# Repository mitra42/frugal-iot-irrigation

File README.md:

# Frugal-IoT Irrigation

This project is intended to provide solar-powered irrigation for small farms. A set of sectors is watered one at a time, once a day. 

The default version waters each sector until its soil reaches a target moisture or a time limit runs out, but it can be 
subclased for more complex per-sector requirements. 

There are tank-level and battery interlocks that stop the whole run, and this also can be customized. 

It is built on top of Frugal-IoT and both the irrigation and MPPT components draw part of their
inspiration from [OSPIT](https://www.apc.org/en/news/meet-ospit-sustainable-energy-and-irrigation-solution-community-networks)
(Lua on the FF-ESP32-OpenMPPT solar charge controller)
- [OSPIT_COMPARISON.md](OSPIT_COMPARISON.md) describes what is different and why.

This release should work in four hardware environments.

* The "FF-ESP32-OpenMPPT solar charge controller" in which case it will run MPPT 
* Our custom board in `hardware` with onboard relays and RS485. 
* A simple off the shelf dev board with hardwired sensors, just edit board definitions in 
  platformio.ini and `wiring` in frugal-iot-irrigation.ino
* A distributed sensor environment, just change the `wiring` in frugal-iot-irrigation.ino 
  to point at the distributed sensors

[Frugal-IoT](https://github.com/mitra42/frugal-iot) brings: WiFi setup from a phone; MQTT; web and phone dashboards; graphing and over-the-air updates.  

Any of the other features of Frugal-IoT can be easily added to your sketch including, off-internet operation, remote sensors, LoRa, or a wide range of other sensors for example for weather. 

## What it does today

- **Up to N irrigation sectors**, run strictly in order, one valve open at a time.
- **Soil moisture per sector** from RS485/Modbus probes sharing one bus, or from simple
  analog capacitive soil sensors.
- Anomaly handling - for instance, a sector whose probe is **not reporting is skipped**
- **Tank level** from a float sender, with two thresholds: one to begin a run, a lower one to
  abort it. "No tank sensor fitted" is kept distinct from "tank empty".
- **Battery interlock** - irrigation stops below a configurable voltage and resumes above a higher
  one.
- Optional **pump** (driven with the valves) and **load output** (e.g. for a router) (switched by the
  battery interlock) on separate pins.
- Optional **OLED**: Displays battery; sector moistures; tank and communicationss status.
- **Solar charge control** - two-stage MPPT tracking with temperature compensation, a hard
  thermal cut-out, and battery-type profiles.
- **Battery reporting** - state of charge and a health estimate inferred from voltage drop.

## Status

**None of the charge control has run on real hardware yet**, so it ships switched off. 

Run the checks in [TESTING.md](TESTING.md) and then turn on `mppt/automatic`

`HARDWARE-QUESTIONS.md` is a list of things we need someone with the OSPIT hardware to
look at and confirm.

## Hardware

Three boards are supported out of the box. See `platformio.ini` for the full pin list.

| Board | Notes |
|---|---|
| **FF-ESP32-OpenMPPT** | the solar charge controller OSPIT runs on. Pin assignments are OSPIT's own |
| **Frugal IoT Irrigation v0.1** | a custom board with Relays, RS485 and battery charging |
| **Lolin S2 Mini** | the same application on a plain dev board, no charging hardware.|
| other | Setting up support for most other boards is trivial, look in the [Frugal-IoT/examples/all](https://github.com/mitra42/frugal-iot/blob/main/examples/all/platformio.ini) for example configuration for many popular boards or [add a new issue](https://github.com/mitra42/frugal-iot-irrigation/issues/new) in this repo.

The `FF-ESP32-OpenMPTT` board has the needed functionality, but is going to be a significantly more expensive solution than the `Frugal IoT Irrigation v0.1` paired, if neccessary, with an off-the-shelf MPPT controller.

You will also need: 12 V valves and a driver for them, one Modbus soil probe per sector, an RS485
transceiver, and optionally a tank float sender and a pump.

The hardware in `hardware` is available as a full set of Gerber and fabrication files, they are designed for use at SLCPCB but could be adapted to any manufacturer (and we would
be happy to add files for other manufacturers). Note this hardware has (as of Oct 2026) yet to be built and tested. 

## Building

### PlatformIO (recommended)

```bash
pio run --environment ff_openmppt          # compile
pio run --target upload -e ff_openmppt     # flash
pio run --target uploadfs -e ff_openmppt   # upload data/ (WiFi passwords etc)
```

The Frugal-IoT library is fetched automatically, so a fresh clone needs nothing set up. 
If you are changing the library at the same time, 
see "Building against a local library" in [CLAUDE.md](CLAUDE.md).

### Arduino IDE

1. Install **Frugal-IoT** from Library Manager (or clone it into your `libraries/` folder).
2. Install the ESP32 board support package.
3. Open `frugal-iot-irrigation.ino` - the whole repository folder is the sketch folder.
4. Under **Tools > Board**, pick the board you have. `platform.h` supplies the right pins for it;
   if your board has no section there, compiling stops with a message telling you so.

`platform.h` is generated from `platformio.ini`. If you change pins there, re-run
`scripts/generate_platform_h.bash`, or the two toolchains will disagree.

## First run

1. Flash, then power up. The device makes its own WiFi network - connect a phone to it.
2. A setup page opens (or browse to `192.168.4.1`). Give it your WiFi name and password.
3. **Irrigation starts switched off.** Turn it on in the **Irrigation** section, and set
   the start time while you are there.

`TESTING.md` walks through commissioning a real board step by step, including calibrating the tank
and the battery. `HARDWARE-QUESTIONS.md` is a list of things we need someone with the OSPIT hardware to look at.

Because not everyone has sun, a multimeter and a fortnight, `docs/` holds three ready-made plans —
[bench](docs/plan-bench.md), [sunny half-day](docs/plan-sunny-session.md),
[days of running](docs/plan-long-run.md) — each a short ordered list of which Parts of `TESTING.md`
to do. Question 9 of `HARDWARE-QUESTIONS.md` picks one. [docs/sleep-test.md](docs/sleep-test.md) is
the one test that needs its own build, on the `sleep-test` branch.

## Licence

Same as Frugal-IoT. The OSPIT algorithms parts of this are derived from are GPL-2.0-or-later,
Copyright (C) 2026 Corinna 'Elektra' Aichele.

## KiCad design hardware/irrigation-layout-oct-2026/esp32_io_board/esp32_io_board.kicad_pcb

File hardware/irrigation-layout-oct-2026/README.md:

# Frugal-IoT Irrigation V0.1

An ESP32 I/O board for irrigation and similar field control: four 12 V relays, RS485 (Modbus), I2C sensors,
two spare GPIOs, and power from 12 V, USB or a single LiPo cell. Designed Oct 2026 for assembly by JLCPCB.
This folder is for review: comments and suggested changes welcome — see "Points for reviewers" below.

## The board

- 100 × 80 mm, 2 layers, 1.6 mm FR-4, 4 × M3 corner holes.
- Relays and their screw terminals along one long edge; field connectors (12 V in, RS485, I2C, GPIOs, OLED)
  along the other; USB-C on the right short edge, LiPo connector on the left.
- Surface-mount parts on the top side, assembled by JLCPCB; relays and terminals are through-hole
  (JLCPCB hand-solders them, or you can).

## Power

- Powered from **12 V** (screw terminal, up to 15 V), **5 V USB-C**, or a **local single LiPo cell** (optional,
  JST-PH, 18650 at most).
- 12 V input: reverse-polarity protection (Schottky), 15 V TVS, then a 5 V buck (AP63205). USB 5 V and the
  buck output are diode-ORed onto the 5 V rail, so either or both can be connected.
- The 5 V rail charges the cell (TP4056; 250 mA, or 500 mA with a solder jumper). The cell has its own
  protection (DW01A + FS8205A: over-charge, over-discharge, over-current/short).
- Load sharing: when 5 V is present it powers the board and the charger only charges; when 5 V goes away a
  P-FET switches the cell in. Either source then feeds a 3.3 V LDO (AP2112K, 600 mA) for the module.
- Two switched rails turned on together by one GPIO: **3V3_SW** (sensors, I2C, RS485) and **5V_SW** (RS485
  sensor supply). Both off at reset. 5V_SW only exists when 12 V or USB is present, not on battery alone.
- Monitoring: the 12 V input and the cell voltage are each read on an ADC pin.
- The relay coils run from 12 V, so **relays work only when 12 V is connected**.

## Processor

- ESP32-C6-MINI-1U module (default) or ESP32-C3-MINI-1U on the same footprint — both have a **U.FL antenna
  socket** (an external antenna is needed). Two pairs of 0 Ω links select which module's USB pins are used.
- Native USB on USB-C for programming and serial (no USB-UART chip); USB ESD protection.
- Buttons: RESET, BOOT/BTN1 (hold at reset for download mode, a normal button afterwards), BTN2 (C6 only).
- Status LED (green); charger LEDs (charging red, charged green).
- Unfitted headers for UART0 debug, a cell thermistor, and the I/O expander's spare pins.

## Outputs and interfaces

- **4 relays** (SRD-12VDC-SL-C), contacts NO/COM/NC on 5.08 mm screw terminals, isolated from the board rails.
  Rated for 12 V DC loads up to about 4–5 A per channel with this copper. Driven through an I2C I/O expander
  (TCA9534) and a ULN2003, so the relays stay off through reset and boot. A red LED per relay shows it is on.
- **RS485** (Modbus): 3.3 V transceiver, not isolated, transmit/receive switched automatically from the TX
  line; bias resistors, 120 Ω termination on a solder jumper, surge protection. Terminal: 5V_SW, A, B, GND.
- **I2C**: 4-way 2.54 mm terminal (3V3_SW, SDA, SCL, GND) plus a 4-pin OLED header (GND, 3V3_SW, SCL, SDA).
- **2 GPIOs** (GPIO_A — ADC capable — and GPIO_B, C6 only) on 2-way 2.54 mm terminals with GND, with
  unfitted pull-up/pull-down positions.

## Firmware notes

- Turn on RAIL_EN before any I2C traffic (relay changes included) or RS485; the expander itself is always
  powered and keeps the relays as set while the rail is off.
- Relay outputs: TCA9534 P0–P3 high = relay on. P4–P7 go to an unfitted header — drive them low if unused.
- GPIO map (module pad → use) is in DECISIONS.md, D18.

## Points for reviewers

Items that are deliberately "proposed" rather than final — opinions especially welcome:

1. RS485 direction from TX (D21): fine for Modbus at 9600 baud, marginal with long cables and two
   terminations; a true auto-direction transceiver (THVD1406) is the alternative.
2. RS485 terminal supplies 5V_SW — should it be 12 V for your sensors? (D22)
3. Cell thermistor (TEMP) disabled by default (D27); charge current 250/500 mA (D12).
4. LiPo connector: pin 1 = −, pin 2 = + (D47). JST-PH polarity is not standard — check your cells.
5. Relay contact copper ~4–5 A per channel (D50).
6. The 5.08 mm terminals use the Phoenix MKDS footprint for KF128 parts of the same pitch (D42).
7. Small bulk capacitance on 3V3_SW to limit inrush (D33).
8. Before ordering: check part rotations in JLCPCB's assembly preview (see fabrication/README.md).

## Cost (JLCPCB, Oct 2026)

About **$22 per board for 10**, **$13 per board for 100**, assembled, before shipping. Breakdown in
COST-ESTIMATE.txt; the ESP32 module is the largest single item.

## What's in this folder

| | |
|---|---|
| `README.md` | This description |
| `SCHEMATIC.pdf` | Full schematic, one sheet |
| `PCB-LAYOUT.pdf` | 3D views and both copper layers |
| `BOM.csv` | Bill of materials with LCSC (JLCPCB) part numbers |
| `COST-ESTIMATE.txt` | JLCPCB cost for 10 and 100 boards |
| `DECISIONS.md` | Every design decision, why, and what would reopen it (D1–D64) |
| `esp32_io_board/` | KiCad 10 project (schematic, PCB, project libraries) |
| `fabrication/` | Files to order from JLCPCB — see its README |
| `firmware/` | PlatformIO env for frugal-iot-irrigation + board variant (pins_arduino.h) |
| `datasheets/` | Datasheets checked during design |
| `claude-tools/` | Scripts Claude uses to regenerate and change the design — reviewers can ignore |

To suggest a change: mark up the PDFs, edit in KiCad, or describe it; the schematic is generated from
`claude-tools/schematic/circuit.py`, so changes made by Claude go there rather than into the .kicad_sch.

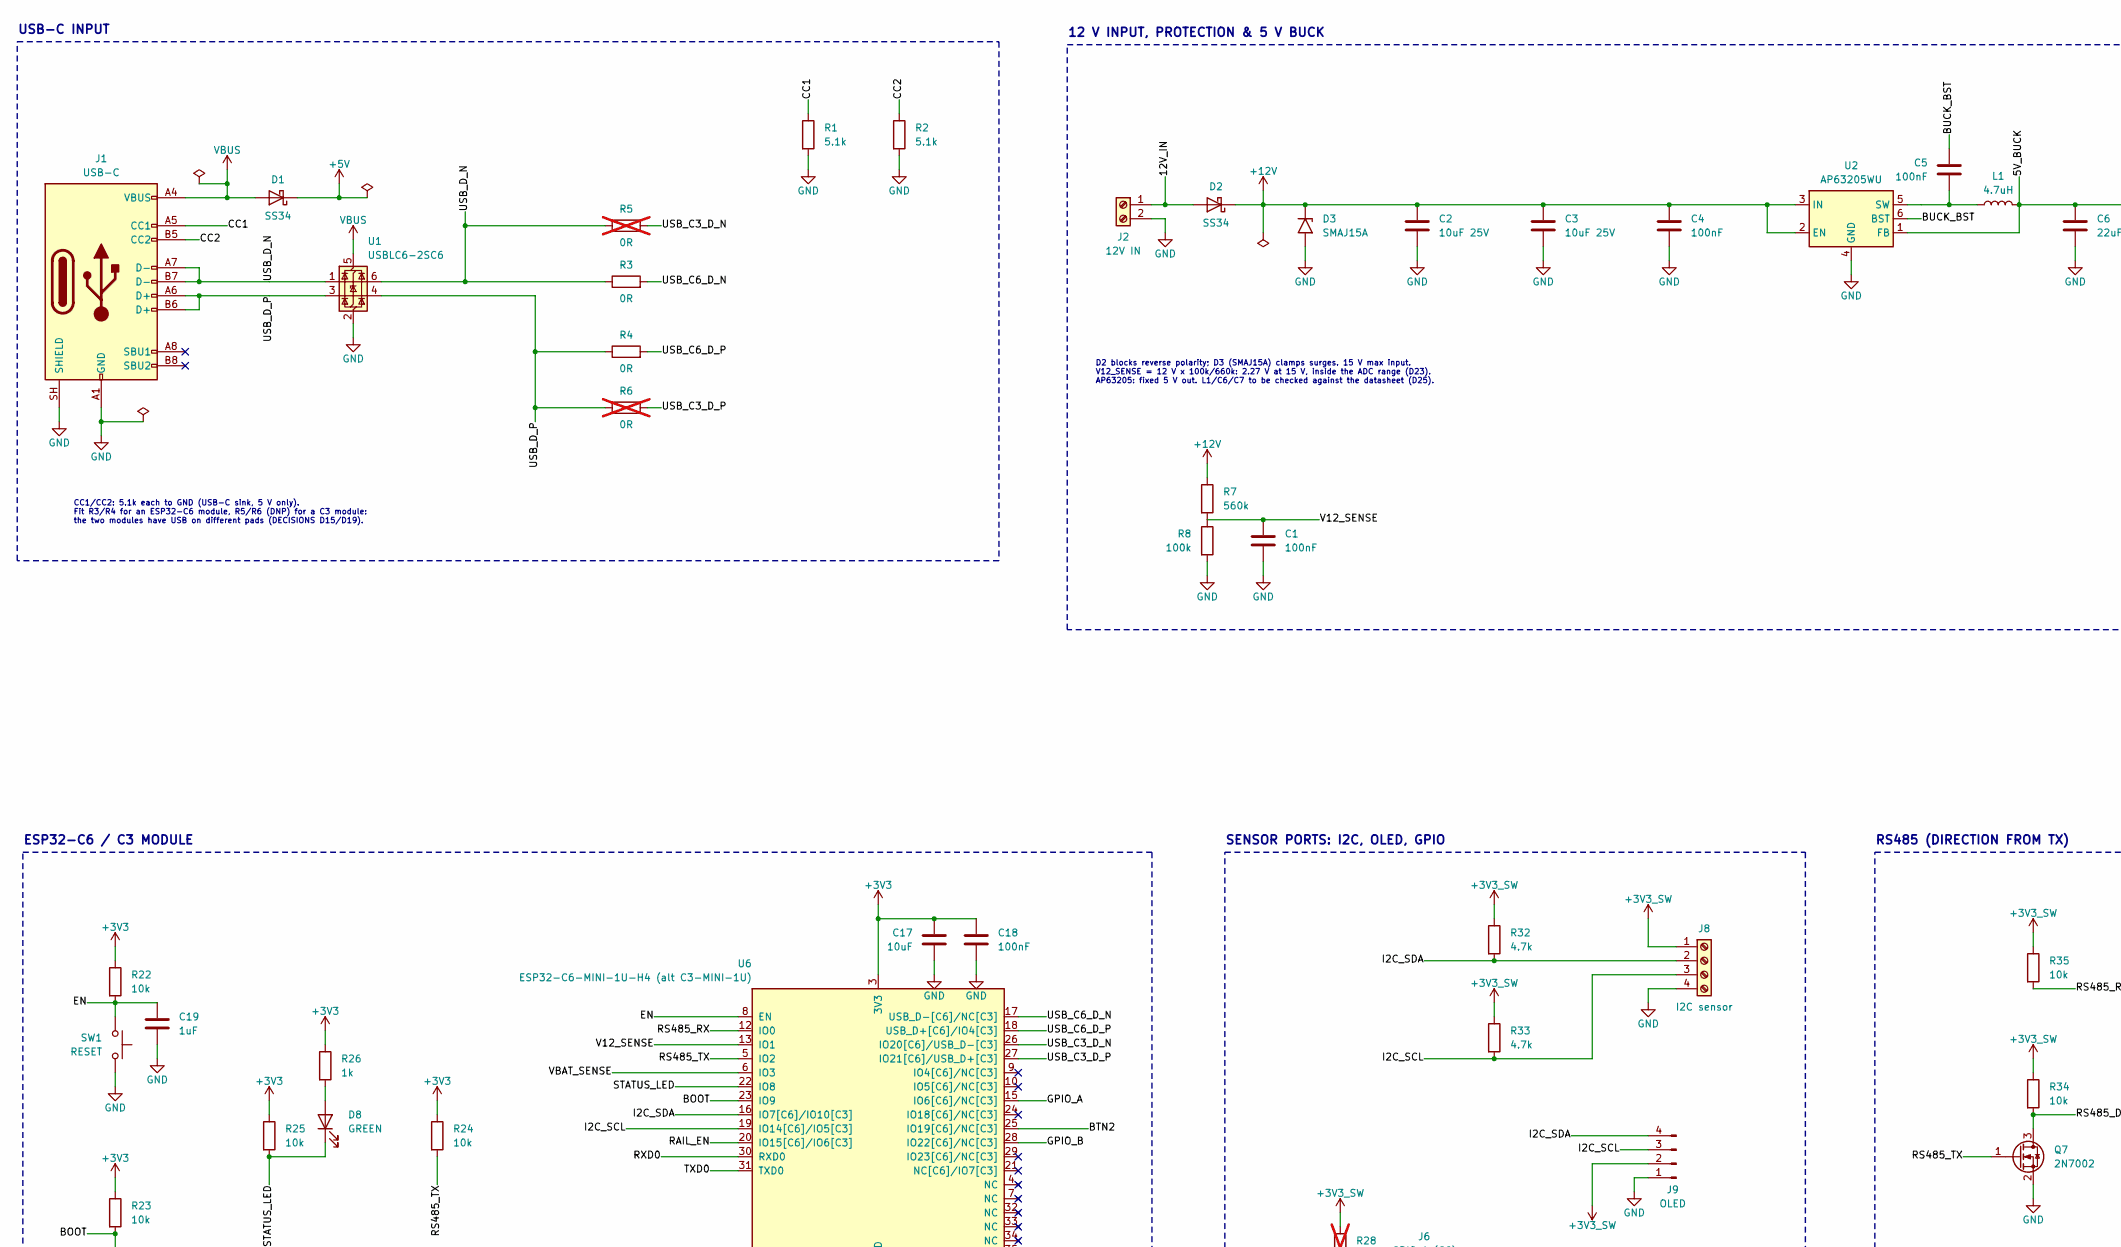
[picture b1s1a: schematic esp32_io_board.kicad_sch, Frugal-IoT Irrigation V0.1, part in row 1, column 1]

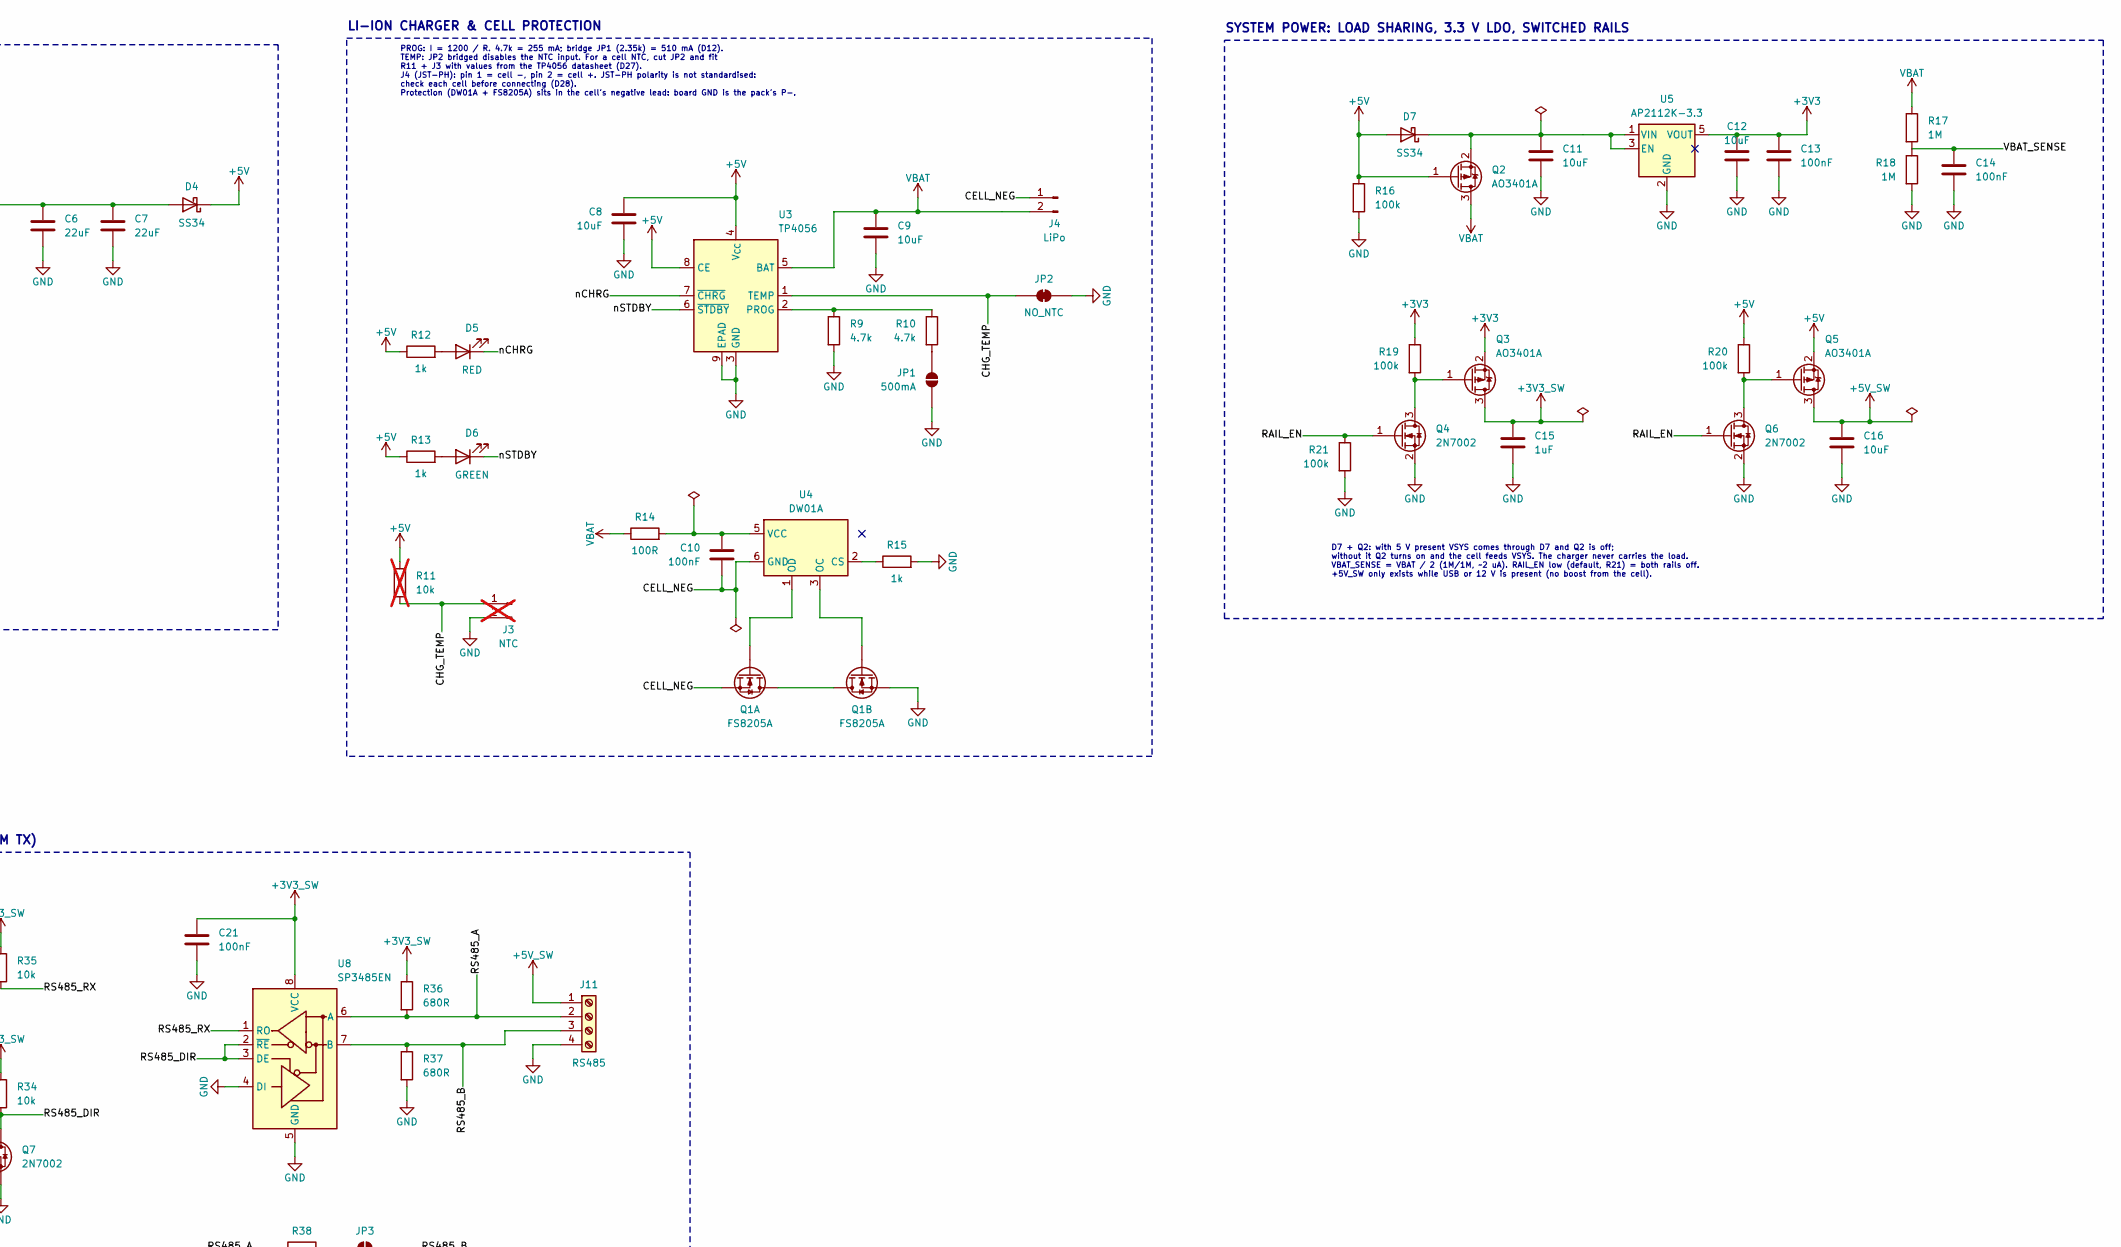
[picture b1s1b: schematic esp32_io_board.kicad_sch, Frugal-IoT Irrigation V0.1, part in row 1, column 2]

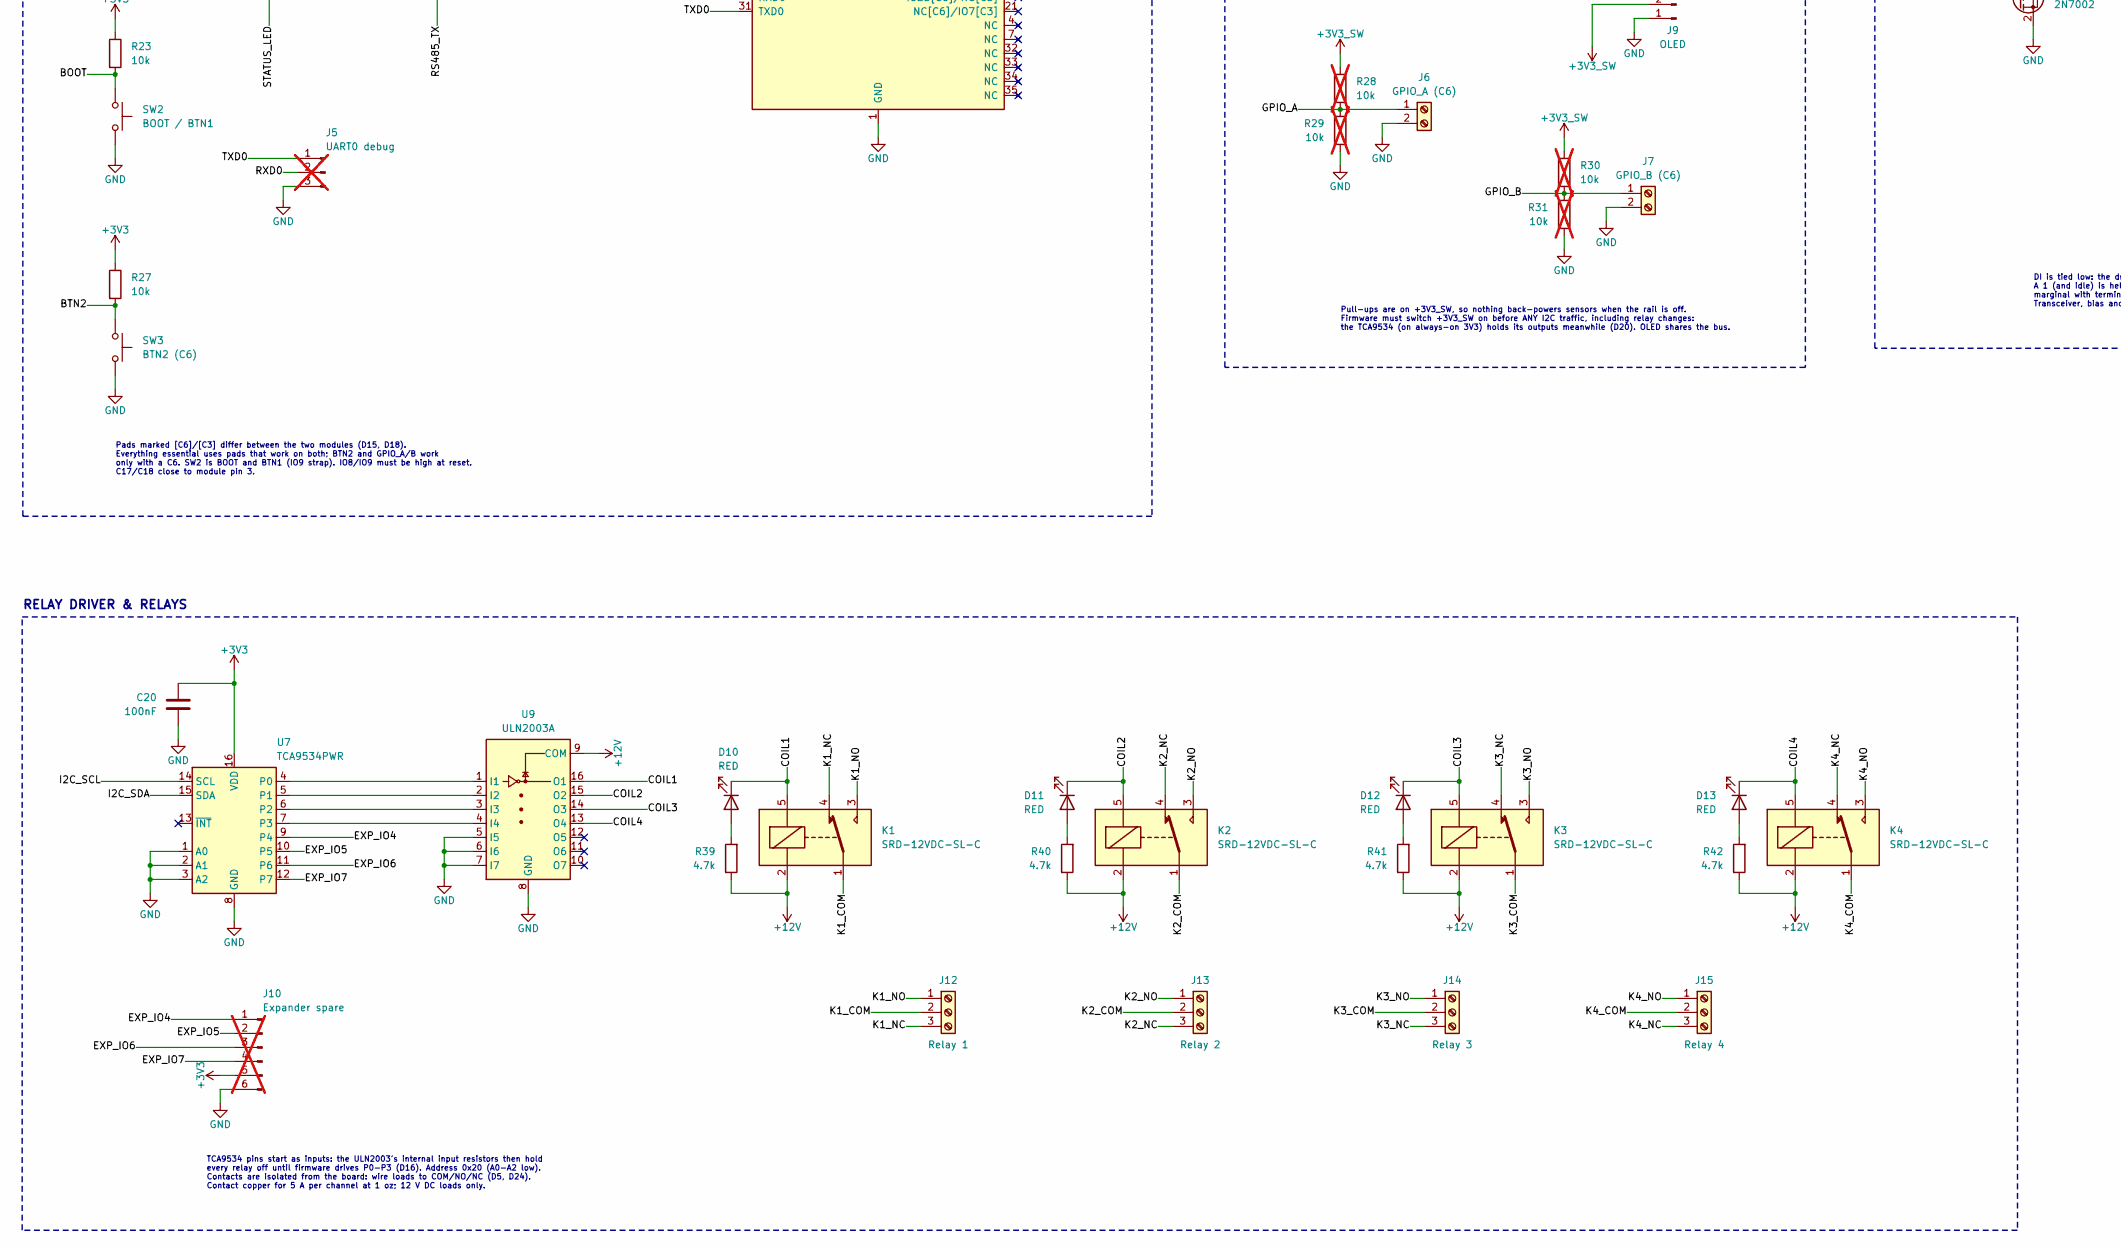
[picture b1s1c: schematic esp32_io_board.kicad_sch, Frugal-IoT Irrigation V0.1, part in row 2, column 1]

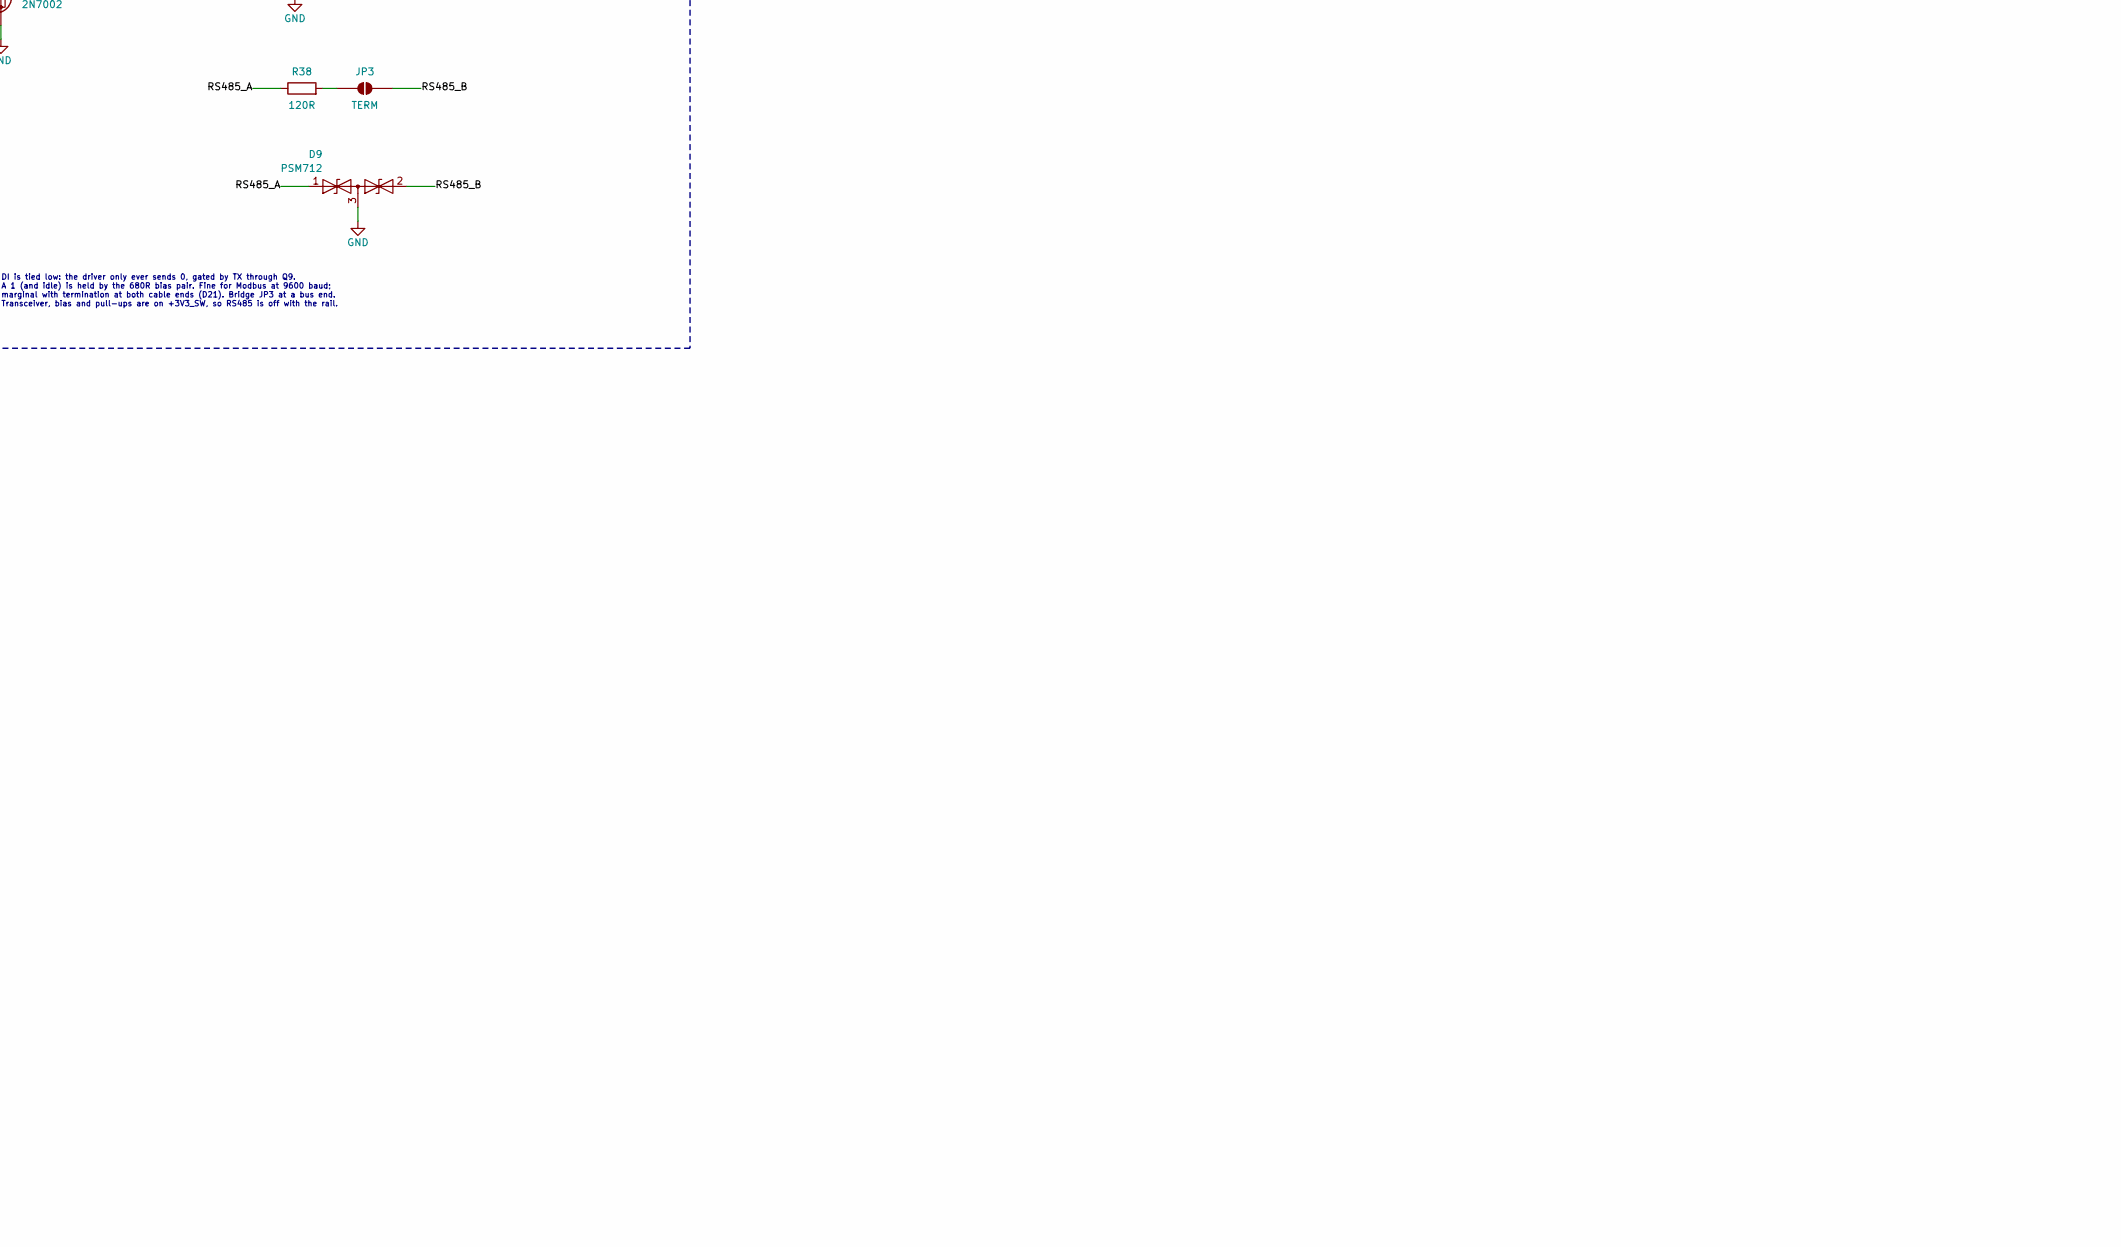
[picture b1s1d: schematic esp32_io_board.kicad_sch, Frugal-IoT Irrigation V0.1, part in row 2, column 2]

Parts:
C1, C4, C5, C10, C13, C14, C18, C20, C21: 100nF; C_0603_1608Metric; MPN 100nF; LCSC C14663
C2, C3: 10uF 25V; C_1206_3216Metric; MPN 10uF 25V; LCSC C13585
C6, C7: 22uF; C_1206_3216Metric; MPN 22uF; LCSC C12891
C8, C9, C11, C12, C16, C17: 10uF; C_0603_1608Metric; MPN 10uF; LCSC C19702
C15, C19: 1uF; C_0603_1608Metric; MPN 1uF; LCSC C15849
D1, D2, D4, D7: SS34; D_SMA; MPN SS34; LCSC C8678
D3: SMAJ15A; D_SMA; MPN SMAJ15A; LCSC C19077535
D5, D10, D11, D12, D13: RED; LED_0603_1608Metric; MPN KT-0603R; LCSC C2286
D6, D8: GREEN; LED_0805_2012Metric; MPN KT-0805G; LCSC C2297
D9: PSM712; SOT-23; MPN PSM712-LF-T7; LCSC C32677
J1: USB-C; USB_C_Receptacle_HRO_TYPE-C-31-M-12; MPN TYPE-C-31-M-12; LCSC C165948
J2: 12V IN; TerminalBlock_Phoenix_MKDS-1,5-2-5.08_1x02_P5.08mm_Horizont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; MPN KF128-5.08-2P; LCSC C474952
J3: NTC; PinHeader_1x02_P2.54mm_Vertical; MPN NTC; not fitted
J4: LiPo; JST_PH_S2B-PH-K_1x02_P2.00mm_Horizontal; MPN S2B-PH-K-S; LCSC C157932
J5: UART0 debug; PinHeader_1x03_P2.54mm_Vertical; MPN UART0 debug; not fitted
J6: GPIO_A (C6); TerminalBlock_Xinya_XY308-2.54-2P_1x02_P2.54mm_Horizontal; MPN XY308-2.54-2P; LCSC C557685
J7: GPIO_B (C6); TerminalBlock_Xinya_XY308-2.54-2P_1x02_P2.54mm_Horizontal; MPN XY308-2.54-2P; LCSC C557685
J8: I2C sensor; TerminalBlock_Xinya_XY308-2.54-4P_1x04_P2.54mm_Horizontal; MPN XY308-2.54-4P; LCSC C915913
J9: OLED; PinHeader_1x04_P2.54mm_Vertical; MPN PZ254V-11-04P; LCSC C492403
J10: Expander spare; PinHeader_1x06_P2.54mm_Vertical; MPN Expander spare; not fitted
J11: RS485; TerminalBlock_Xinya_XY308-2.54-4P_1x04_P2.54mm_Horizontal; MPN XY308-2.54-4P; LCSC C915913
J12: Relay 1; TerminalBlock_Phoenix_MKDS-1,5-3-5.08_1x03_P5.08mm_Horizont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; MPN KF128-5.08-3P; LCSC C474953
J13: Relay 2; TerminalBlock_Phoenix_MKDS-1,5-3-5.08_1x03_P5.08mm_Horizont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; MPN KF128-5.08-3P; LCSC C474953
J14: Relay 3; TerminalBlock_Phoenix_MKDS-1,5-3-5.08_1x03_P5.08mm_Horizont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; MPN KF128-5.08-3P; LCSC C474953
J15: Relay 4; TerminalBlock_Phoenix_MKDS-1,5-3-5.08_1x03_P5.08mm_Horizont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; MPN KF128-5.08-3P; LCSC C474953
JP1: 500mA; SolderJumper-2_P1.3mm_Open_RoundedPad1.0x1.5mm; MPN 500mA
JP2: NO_NTC; SolderJumper-2_P1.3mm_Bridged_RoundedPad1.0x1.5mm; MPN NO_NTC
JP3: TERM; SolderJumper-2_P1.3mm_Open_RoundedPad1.0x1.5mm; MPN TERM
K1, K2, K3, K4: SRD-12VDC-SL-C; Relay_SPDT_SANYOU_SRD_Series_Form_C; MPN SRD-12VDC-SL-C; LCSC C30431
L1: 4.7uH; L_Sunlord_SWPA5040S; MPN SWPA5040S4R7NT; LCSC C305174
Q1: FS8205A; SOT-23-6; MPN FS8205A; LCSC C908265
Q2, Q3, Q5: AO3401A; SOT-23; MPN AO3401A; LCSC C15127
Q4, Q6, Q7: 2N7002; SOT-23; MPN 2N7002; LCSC C8545
R1, R2: 5.1k; R_0603_1608Metric; MPN 5.1k; LCSC C23186
R3, R4: 0R; R_0603_1608Metric; MPN 0R; LCSC C21189
R5, R6: 0R; R_0603_1608Metric; MPN 0R; LCSC C21189; not fitted
R7: 560k; R_0603_1608Metric; MPN 560k; LCSC C23203
R8, R16, R19, R20, R21: 100k; R_0603_1608Metric; MPN 100k; LCSC C25803
R9, R10, R32, R33, R39, R40, R41, R42: 4.7k; R_0603_1608Metric; MPN 4.7k; LCSC C23162
R11, R28, R29, R30, R31: 10k; R_0603_1608Metric; MPN 10k; LCSC C25804; not fitted
R12, R13, R15, R26: 1k; R_0603_1608Metric; MPN 1k; LCSC C21190
R14: 100R; R_0603_1608Metric; MPN 100R; LCSC C22775
R17, R18: 1M; R_0603_1608Metric; MPN 1M; LCSC C22935
R22, R23, R24, R25, R27, R34, R35: 10k; R_0603_1608Metric; MPN 10k; LCSC C25804
R36, R37: 680R; R_0603_1608Metric; MPN 680R; LCSC C23228
R38: 120R; R_0603_1608Metric; MPN 120R; LCSC C22787
SW1: RESET; SW_Push_1P1T_XKB_TS-1187A; MPN TS-1187A-B-A-B; LCSC C318884
SW2: BOOT / BTN1; SW_Push_1P1T_XKB_TS-1187A; MPN TS-1187A-B-A-B; LCSC C318884
SW3: BTN2 (C6); SW_Push_1P1T_XKB_TS-1187A; MPN TS-1187A-B-A-B; LCSC C318884
U1: USBLC6-2SC6; SOT-23-6; MPN USBLC6-2SC6; LCSC C7519
U2: AP63205WU; TSOT-23-6; MPN AP63205WU-7; LCSC C2071056
U3: TP4056; SOIC-8-1EP_3.9x4.9mm_P1.27mm_EP2.41x3.3mm; MPN TP4056; LCSC C16581
U4: DW01A; SOT-23-6; MPN DW01A; LCSC C351410
U5: AP2112K-3.3; SOT-23-5; MPN AP2112K-3.3; LCSC C51118
U6: ESP32-C6-MINI-1U-H4 (alt C3-MINI-1U); ESP32-C3-C6-MINI-1U; MPN ESP32-C6-MINI-1U-H4; LCSC C20627095
U7: TCA9534PWR; TSSOP-16_4.4x5mm_P0.65mm; MPN TCA9534PWR; LCSC C783615
U8: SP3485EN; SOIC-8_3.9x4.9mm_P1.27mm; MPN SP3485EN-L/TR; LCSC C8963
U9: ULN2003A; SOIC-16_3.9x9.9mm_P1.27mm; MPN ULN2003ADR; LCSC C7512

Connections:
+3V3: C12.1, C13.1, C17.1, C18.1, C20.1, J10.5, Q3.2 (S), R19.1, R22.1, R23.1, R24.1, R25.1, R26.1, R27.1, U5.5 (VOUT), U6.3 (3V3), U7.16 (VDD)
/5V_BUCK: C6.1, C7.1, D4.2 (A), L1.2, U2.1 (FB)
/12V_IN: D2.2 (A), J2.1
/BOOT: R23.2, SW2.1, U6.23 (IO9)
/BTN2: R27.2, SW3.1, U6.25 (IO19[C6]/NC[C3])
/BUCK_BST: C5.1, U2.6 (BST)
/CC1: J1.A5 (CC1), R1.1
/CC2: J1.B5 (CC2), R2.1
/CHG_TEMP: J3.1, JP2.1 (A), R11.2, U3.1 (TEMP)
/COIL1: D10.1 (K), K1.5, U9.16 (O1)
/COIL2: D11.1 (K), K2.5, U9.15 (O2)
/COIL3: D12.1 (K), K3.5, U9.14 (O3)
/COIL4: D13.1 (K), K4.5, U9.13 (O4)
/EN: C19.1, R22.2, SW1.1, U6.8 (EN)
/EXP_IO4: J10.1, U7.9 (P4)
/EXP_IO5: J10.2, U7.10 (P5)
/EXP_IO6: J10.3, U7.11 (P6)
/EXP_IO7: J10.4, U7.12 (P7)
/GPIO_A: J6.1, R28.2, R29.1, U6.15 (IO6[C6]/NC[C3])
/GPIO_B: J7.1, R30.2, R31.1, U6.28 (IO22[C6]/NC[C3])
/I2C_SCL: J8.3, J9.3, R33.2, U6.19 (IO14[C6]/IO5[C3]), U7.14 (SCL)
/I2C_SDA: J8.2, J9.4, R32.2, U6.16 (IO7[C6]/IO10[C3]), U7.15 (SDA)
/K1_COM: J12.2, K1.1
/K1_NC: J12.3, K1.4
/K1_NO: J12.1, K1.3
/K2_COM: J13.2, K2.1
/K2_NC: J13.3, K2.4
/K2_NO: J13.1, K2.3
/K3_COM: J14.2, K3.1
/K3_NC: J14.3, K3.4
/K3_NO: J14.1, K3.3
/K4_COM: J15.2, K4.1
/K4_NC: J15.3, K4.4
/K4_NO: J15.1, K4.3
/RAIL_EN: Q4.1 (G), Q6.1 (G), R21.1, U6.20 (IO15[C6]/IO6[C3])
/RS485_A: D9.1 (A1), J11.2, R36.2, R38.1, U8.6 (A)
/RS485_B: D9.2 (A2), J11.3, JP3.2 (B), R37.1, U8.7 (B)
/RS485_DIR: Q7.3 (D), R34.2, U8.2 (~RE), U8.3 (DE)
/RS485_RX: R35.2, U6.12 (IO0), U8.1 (RO)
/RS485_TX: Q7.1 (G), R24.2, U6.5 (IO2)
/RXD0: J5.2, U6.30 (RXD0)
/STATUS_LED: D8.1 (K), R25.2, U6.22 (IO8)
/TXD0: J5.1, U6.31 (TXD0)
/USB_C3_D_N: R5.2, U6.26 (IO20[C6]/USB_D-[C3])
/USB_C3_D_P: R6.2, U6.27 (IO21[C6]/USB_D+[C3])
/USB_C6_D_N: R3.2, U6.17 (USB_D-[C6]/NC[C3])
/USB_C6_D_P: R4.2, U6.18 (USB_D+[C6]/IO4[C3])
/USB_D_N: J1.A7 (D-), J1.B7 (D-), R3.1, R5.1, U1.1 (I/O1), U1.6 (I/O1)
/USB_D_P: J1.A6 (D+), J1.B6 (D+), R4.1, R6.1, U1.3 (I/O2), U1.4 (I/O2)
/V12_SENSE: C1.1, R7.2, R8.1, U6.13 (IO1)
/VBAT_SENSE: C14.1, R17.2, R18.1, U6.6 (IO3)
/nCHRG: D5.1 (K), U3.7 (~CHRG)
/nSTDBY: D6.1 (K), U3.6 (~STDBY)
unnamed: D5.2 (A), R12.2
unnamed: D6.2 (A), R13.2
unnamed: D8.2 (A), R26.2
unnamed: D10.2 (A), R39.2
unnamed: D11.2 (A), R40.2
unnamed: D12.2 (A), R41.2
unnamed: D13.2 (A), R42.2
unnamed: JP1.1 (A), R10.2
unnamed: JP3.1 (A), R38.2
unnamed: Q1.2 (D), Q1.5 (D)
unnamed: Q1.6 (G), U4.1 (OD)
unnamed: Q1.4 (G), U4.3 (OC)
unnamed: Q3.1 (G), Q4.3 (D), R19.2
unnamed: Q5.1 (G), Q6.3 (D), R20.2
unnamed: C5.2, L1.1, U2.5 (SW)
unnamed: R9.1, R10.1, U3.2 (PROG)
unnamed: R15.1, U4.2 (CS)
unnamed: U7.4 (P0), U9.1 (I1)
unnamed: U7.5 (P1), U9.2 (I2)
unnamed: U7.6 (P2), U9.3 (I3)
unnamed: U7.7 (P3), U9.4 (I4)
VBAT: C9.1, J4.2, Q2.3 (D), R14.1, R17.1, U3.5 (BAT)

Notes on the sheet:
CC1/CC2: 5.1k each to GND (USB-C sink, 5 V only). Fit R3/R4 for an ESP32-C6 module, R5/R6 (DNP) for a C3 module: the two modules have USB on different pads (DECISIONS D15/D19).
RS485 (DIRECTION FROM TX)
SYSTEM POWER: LOAD SHARING, 3.3 V LDO, SWITCHED RAILS
Pull-ups are on +3V3_SW, so nothing back-powers sensors when the rail is off. Firmware must switch +3V3_SW on before ANY I2C traffic, including relay changes: the TCA9534 (on always-on 3V3) holds its outputs meanwhile (D20). OLED shares the bus.
12 V INPUT, PROTECTION & 5 V BUCK
TCA9534 pins start as inputs: the ULN2003's internal input resistors then hold every relay off until firmware drives P0-P3 (D16). Address 0x20 (A0-A2 low). Contacts are isolated from the board: wire loads to COM/NO/NC (D5, D24). Contact copper for 5 A per channel at 1 oz; 12 V DC loads only.
USB-C INPUT
Pads marked [C6]/[C3] differ between the two modules (D15, D18). Everything essential uses pads that work on both; BTN2 and GPIO_A/B work only with a C6. SW2 is BOOT and BTN1 (IO9 strap). IO8/IO9 must be high at reset. C17/C18 close to module pin 3.
D2 blocks reverse polarity; D3 (SMAJ15A) clamps surges. 15 V max input. V12_SENSE = 12 V x 100k/660k: 2.27 V at 15 V, inside the ADC range (D23). AP63205: fixed 5 V out. L1/C6/C7 to be checked against the datasheet (D25).
PROG: I = 1200 / R. 4.7k = 255 mA; bridge JP1 (2.35k) = 510 mA (D12). TEMP: JP2 bridged disables the NTC input. For a cell NTC, cut JP2 and fit R11 + J3 with values from the TP4056 datasheet (D27). J4 (JST-PH): pin 1 = cell -, pin 2 = cell +. JST-PH polarity is not standardised: check each cell bef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
DI is tied low: the driver only ever sends 0, gated by TX through Q9. A 1 (and idle) is held by the 680R bias pair. Fine for Modbus at 9600 baud; marginal with termination at both cable ends (D21). Bridge JP3 at a bus end. Transceiver, bias and pull-ups are on +3V3_SW, so RS485 is off with the rail.
LI-ION CHARGER & CELL PROTECTION
RELAY DRIVER & RELAYS
SENSOR PORTS: I2C, OLED, GPIO
ESP32-C6 / C3 MODULE
D7 + Q2: with 5 V present VSYS comes through D7 and Q2 is off; without it Q2 turns on and the cell feeds VSYS. The charger never carries the load. VBAT_SENSE = VBAT / 2 (1M/1M, ~2 uA). RAIL_EN low (default, R21) = both rails off. +5V_SW only exists while USB or 12 V is present (no boost from the ce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
